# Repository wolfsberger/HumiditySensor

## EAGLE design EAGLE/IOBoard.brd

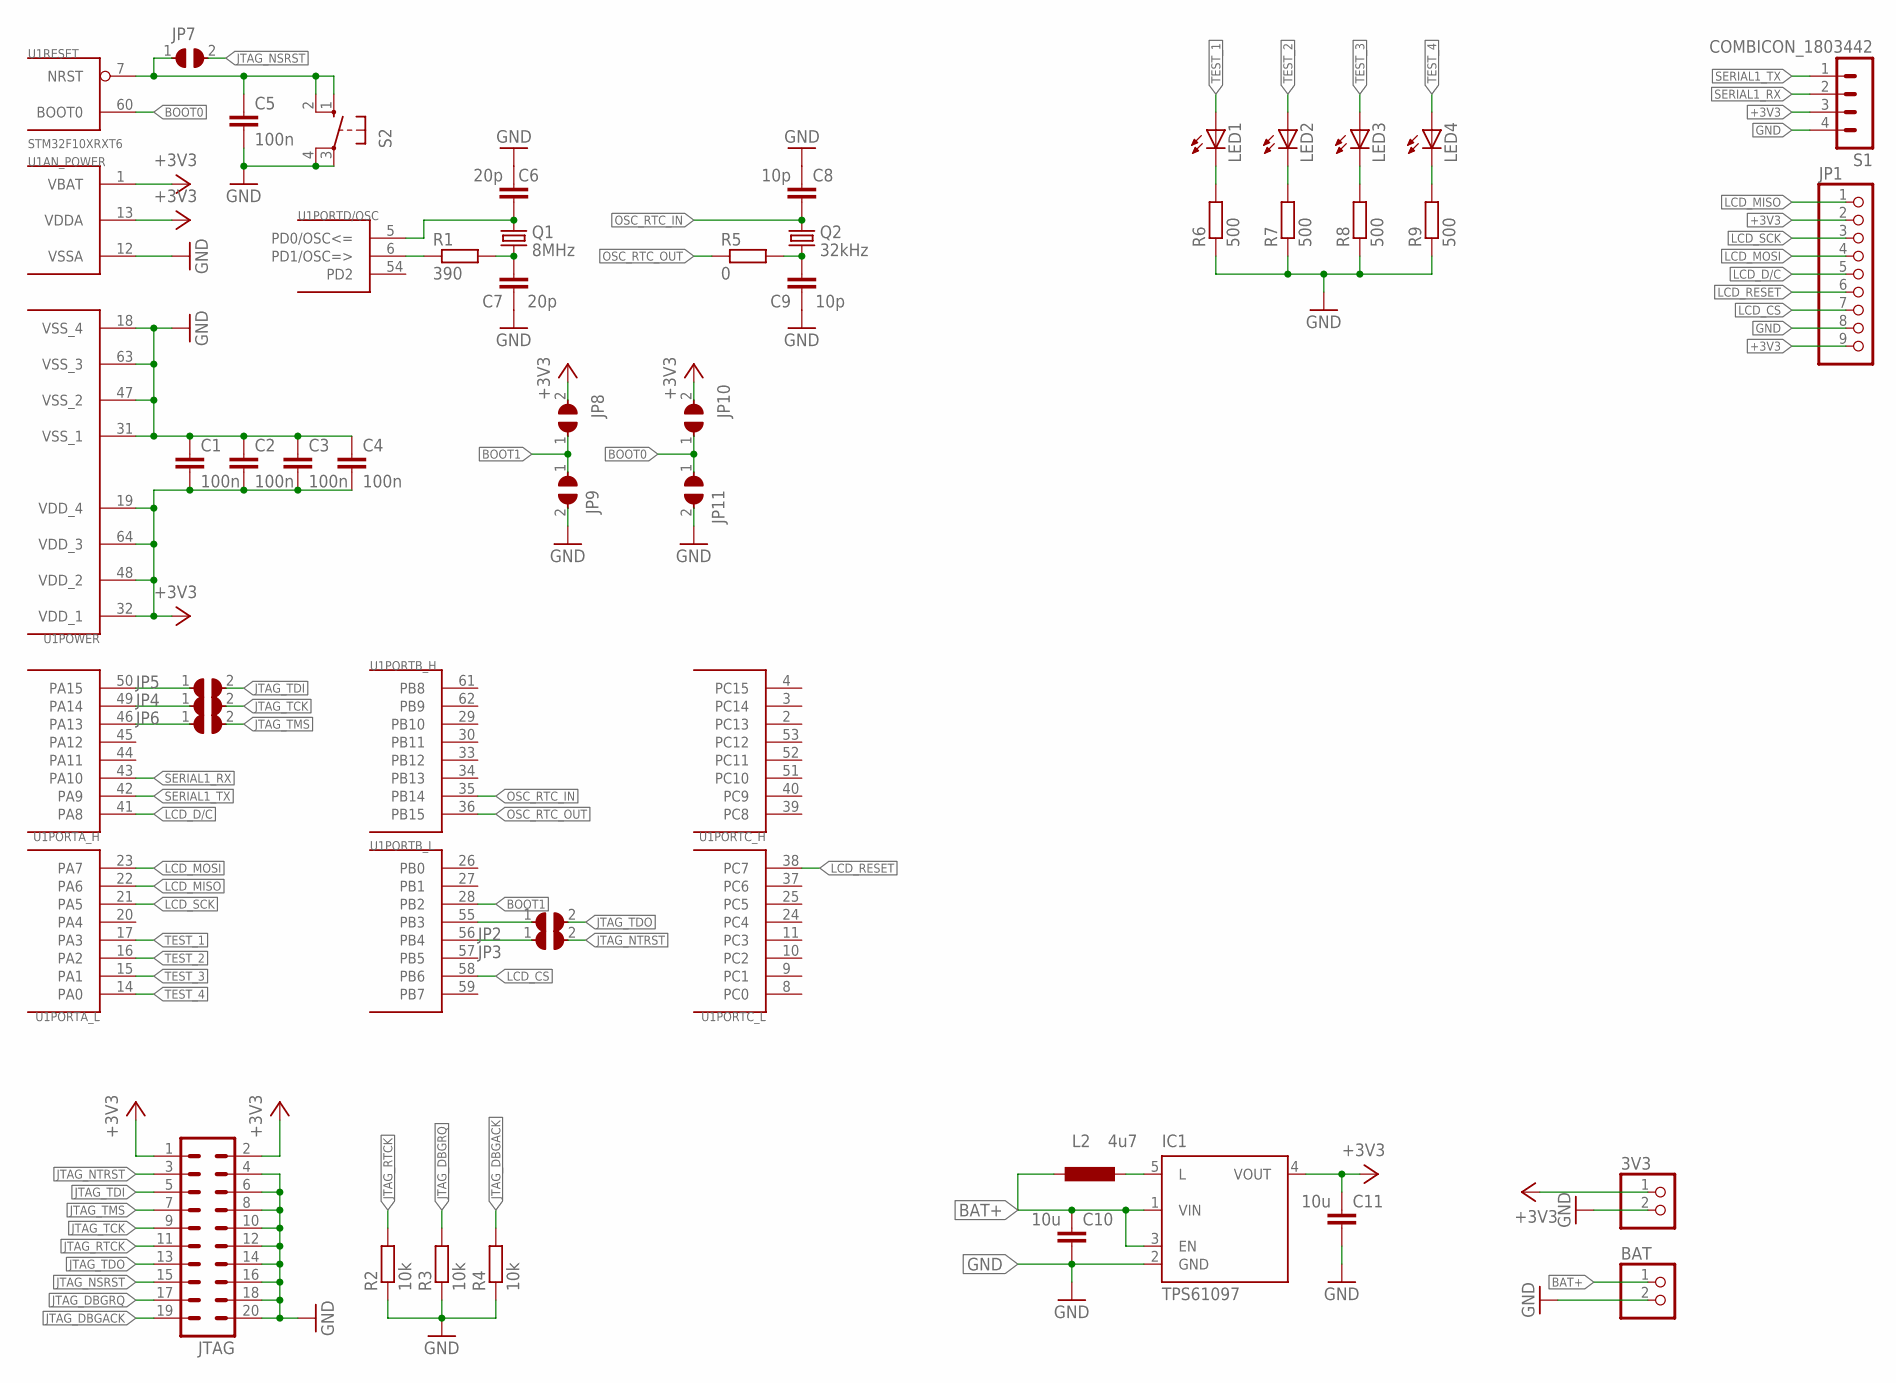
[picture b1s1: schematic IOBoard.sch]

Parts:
3V3: PINHD-1X2; 1X02
BAT: PINHD-1X2; 1X02
C1, C2, C3, C4, C5: 100n; C0805
C6, C7: 20p; C0805
C8, C9: 10p; C0805
C10, C11: 10u; C0805
IC1: TPS61097; SOT23-DBV
JP1: PINHD-1X9; 1X09
JP2, JP3, JP4, JP5, JP6, JP7, JP8, JP9, JP10, JP11: JUMPER_SMALL; JUMPER
JTAG: ML20
L2: 4u7; INDC6350X200N
LED1, LED2, LED3, LED4: LEDSML0603; SML0603
Q1: 8MHz; CSM-7X-DU
Q2: 32kHz; MC-306
R1: 390; R0805
R2, R3, R4: 10k; R0805
R5: 0; R0805
R6, R7, R8, R9: 500; R0805
S1: COMBICON_1803442
S2: 10-XX; B3F-10XX
U1: STM32F10XRXT6; TQFP64

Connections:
+3V3: 3V3.1, C1.2, C2.2, C3.2, C4.2, C11.2, IC1.4 (VOUT), JP1.2, JP1.9, JP8.2, JP10.2, JTAG.1, JTAG.2, S1.3, U1.1 (VBAT), U1.13 (VDDA), U1.19 (VDD_4), U1.32 (VDD_1), U1.48 (VDD_2), U1.64 (VDD_3)
BAT+: BAT.1, C10.2, IC1.1 (VIN), IC1.3 (EN), L2.1
BOOT0: JP10.1, JP11.1, U1.60 (BOOT0)
BOOT1: JP8.1, JP9.1, U1.28 (PB2)
GND: 3V3.2, BAT.2, C1.1, C2.1, C3.1, C4.1, C5.2, C6.2, C7.1, C8.2, C9.1, C10.1, C11.1, IC1.2 (GND), JP1.8, JP9.2, JP11.2, JTAG.4, JTAG.6, JTAG.8, JTAG.10, JTAG.12, JTAG.14, JTAG.16, JTAG.18, JTAG.20, R2.1, R3.1, R4.1, R6.1, R7.1, R8.1, R9.1, S1.4, S2.3, S2.4 (P1), U1.12 (VSSA), U1.18 (VSS_4), U1.31 (VSS_1), U1.47 (VSS_2), U1.63 (VSS_3)
JTAG_DBGACK: JTAG.19, R4.2
JTAG_DBGRQ: JTAG.17, R3.2
JTAG_NSRST: JP7.2, JTAG.15
JTAG_NTRST: JP3.2, JTAG.3
JTAG_RTCK: JTAG.11, R2.2
JTAG_TCK: JP4.2, JTAG.9
JTAG_TDI: JP5.2, JTAG.5
JTAG_TDO: JP2.2, JTAG.13
JTAG_TMS: JP6.2, JTAG.7
LCD_CS: JP1.7, U1.58 (PB6)
LCD_D/C: JP1.5, U1.41 (PA8)
LCD_MISO: JP1.1, U1.22 (PA6)
LCD_MOSI: JP1.4, U1.23 (PA7)
LCD_RESET: JP1.6, U1.38 (PC7)
LCD_SCK: JP1.3, U1.21 (PA5)
unnamed: C5.1, JP7.1, S2.1 (S), S2.2 (S1), U1.7 (NRST)
unnamed: C6.1, Q1.2, U1.5 (PD0/OSC<=)
unnamed: R1.1, U1.6 (PD1/OSC=>)
unnamed: JP2.1, U1.55 (PB3)
unnamed: C7.2, Q1.1, R1.2
unnamed: JP4.1, U1.49 (PA14)
unnamed: JP6.1, U1.46 (PA13)
unnamed: JP5.1, U1.50 (PA15)
unnamed: JP3.1, U1.56 (PB4)
unnamed: C9.2, Q2.1, R5.2
unnamed: LED1.C, R6.2
unnamed: LED2.C, R7.2
unnamed: LED3.C, R8.2
unnamed: LED4.C, R9.2
unnamed: IC1.5 (L), L2.2
OSC_RTC_IN: C8.1, Q2.4 (2), U1.35 (PB14)
OSC_RTC_OUT: R5.1, U1.36 (PB15)
SERIAL1_RX: S1.2, U1.43 (PA10)
SERIAL1_TX: S1.1, U1.42 (PA9)
TEST_1: LED1.A, U1.17 (PA3)
TEST_2: LED2.A, U1.16 (PA2)
TEST_3: LED3.A, U1.15 (PA1)
TEST_4: LED4.A, U1.14 (PA0)

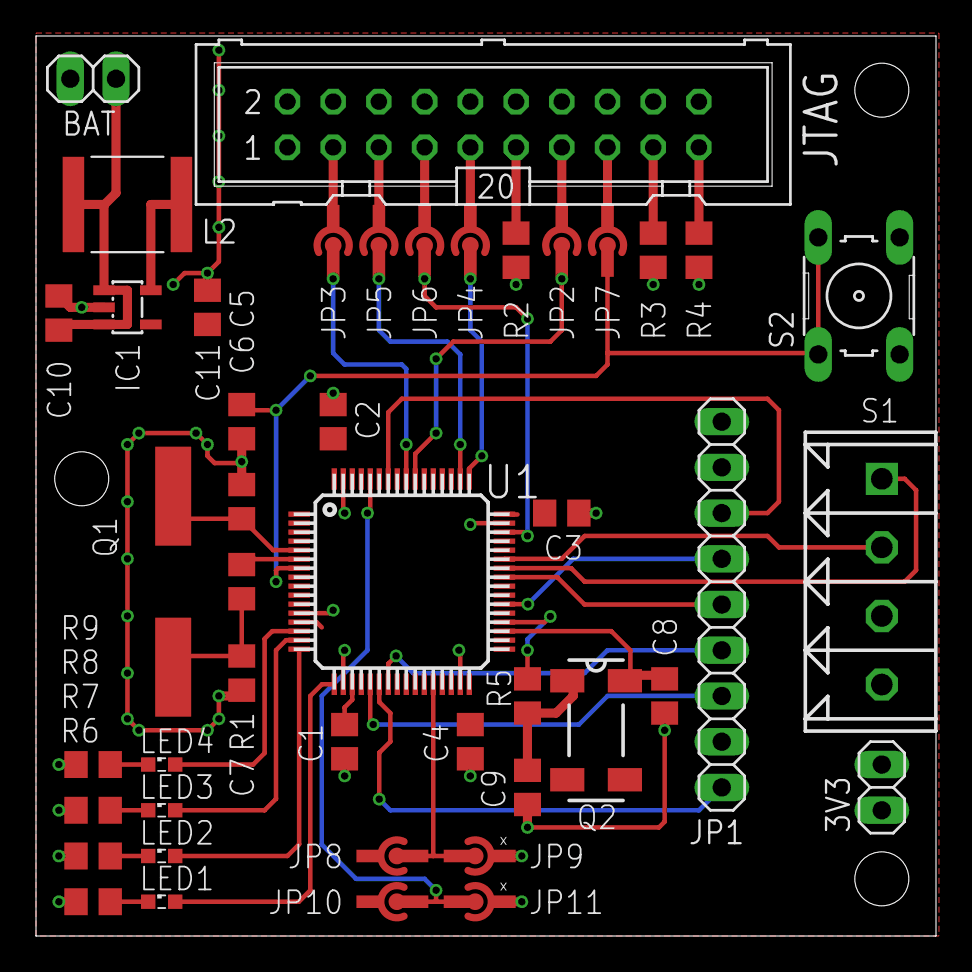
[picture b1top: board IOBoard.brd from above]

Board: 2 copper layers, 50.0 x 50.0 mm, 45 parts (0 on the bottom side), 43 nets.

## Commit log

2016-02-17 Created repository
2016-02-17 Fixed bug
2016-02-18 Added Dewpoint to linegraph
2016-02-19 Implemented a command handler to switch between displayed graphs
2016-02-19 deleted unused files
2016-02-22 Changed not drawn value to NAN
2016-02-22 Added EAGLE files
2016-02-22 Changed .gitignore to filter EAGLE backup files
2016-02-23 Added +3.3V plane to circuit board.
2016-02-23 Fixed bug with NAN
2016-02-23 Finished first prototype of the circuit board
2016-02-24 Created gerber files
2016-02-25 Added a encoder library
